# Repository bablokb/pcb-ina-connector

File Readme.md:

PCB INA-Connector
=================

This is a support PCB for Adafruit's INA219, INA260 and INA3221
breakouts. Connect the power-source to one of the connectors
on the V-IN side, the load to one of the connectors on the V-OUT
side and the INA-breakout to the screwterminal on the back.

V-IN supports

  - a JST-PH2 connector (typically for a LiPo) or
  - a two-pin DuPont 2.54mm pitch header or
  - a 5.5/2.1mm barrel jack

V-OUT suports

  - an AKL-182 socket or
  - a two-pin DuPont 2.54mm pitch header
    
The AKL-182 socket takes AKL-169 plugs. I use these with various
adapter wires, equiped e.g. with micro-USB, USB-C, JST-PH2 on the
other end.
As an alternative, you could use plain 3.5mm screw-terminals.

The footprint inbetween V-IN and V-OUT is for a mini toggle
switch, e.g.
<https://aliexpress.com/item/1005004692981776.html>.

You should also connect GND of this PCB to the INA-breakout if it
does not share GND somewhere else. Likewise for the INA3221
(which has three channels), use and connect three of these
PCBs:

Schematic
---------

Layout
------

3D-Views
--------

3D-Model
--------

In the directory `3D` there is an OpenSCAD-model for a
holder that takes an INA3221 and three off the PCBs.

License
-------

[![CC BY-SA 4.0][cc-by-sa-shield]][cc-by-sa]

This work is licensed under a
[Creative Commons Attribution-ShareAlike 4.0 International
License][cc-by-sa].

[![CC BY-SA 4.0][cc-by-sa-image]][cc-by-sa]

[cc-by-sa]: http://creativecommons.org/licenses/by-sa/4.0/
[cc-by-sa-image]: https://licensebuttons.net/l/by-sa/4.0/88x31.png
[cc-by-sa-shield]:
https://img.shields.io/badge/License-CC%20BY--SA%204.0-lightgrey.svg

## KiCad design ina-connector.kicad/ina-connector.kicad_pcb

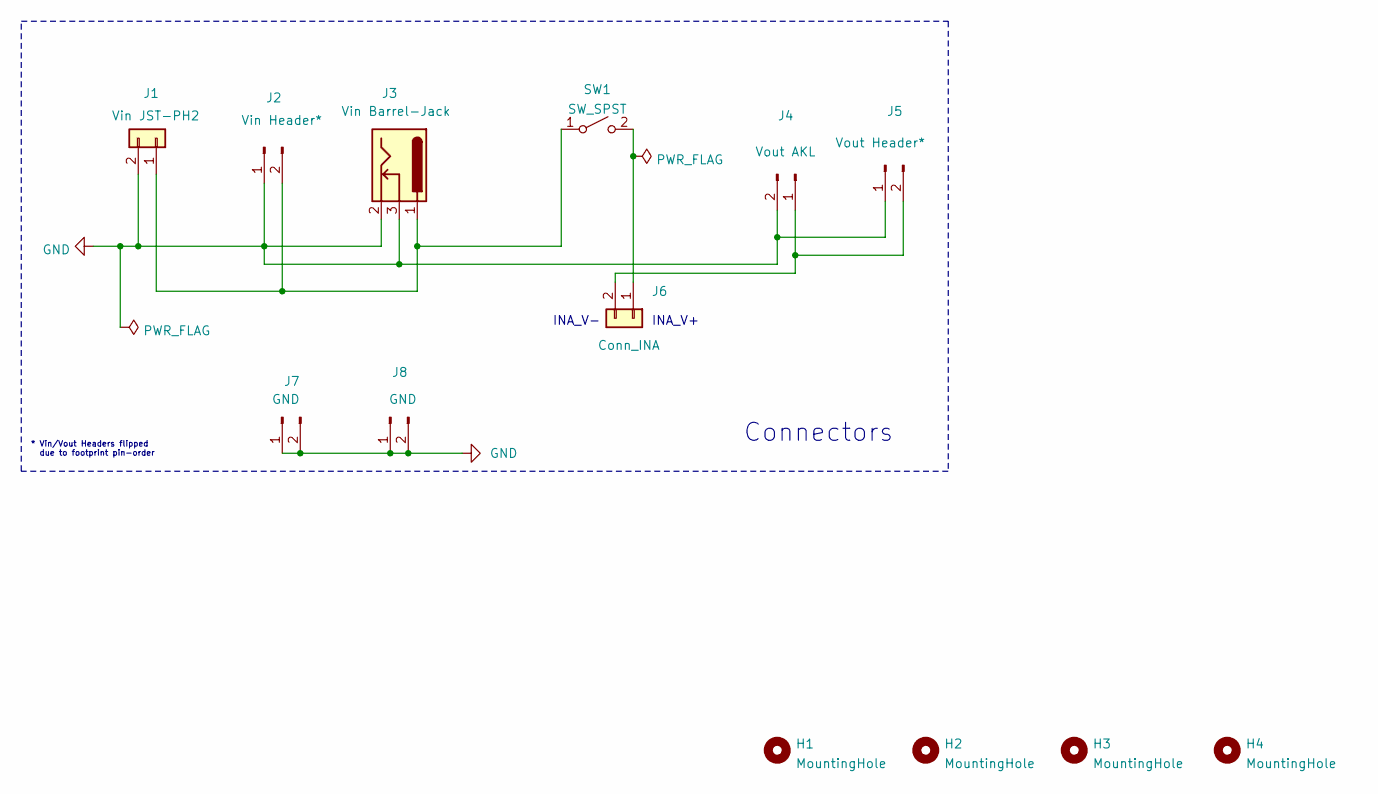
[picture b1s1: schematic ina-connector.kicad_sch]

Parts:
H1, H2, H3, H4: MountingHole; MountingHole_2.5mm
J1: Vin JST-PH2; JST_PH_S2B-PH-SM4-TB_1x02-1MP_P2.00mm_Horizontal
J2: Vin Header*; PinHeader_1x02_P2.54mm_Horizontal
J3: Vin Barrel-Jack; BarrelJack_CUI_PJ-102AH_Horizontal
J4: Vout AKL; TerminalBlock_MetzConnect_Type182_PT11302HBBN_1x02_P3.50mm_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
J5: Vout Header*; PinHeader_1x02_P2.54mm_Horizontal
J6: Conn_INA; TerminalBlock_MetzConnect_Type059_RT06302HBWC_1x02_P3.50mm_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
J7, J8: GND; PinHeader_1x02_P2.54mm_Horizontal
SW1: SW_SPST; Kippschalter_On-Off

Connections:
GND: J1.2, J2.1, J3.2, J3.3, J4.2, J5.1, J7.1, J7.2, J8.1, J8.2
unnamed: J1.1, J2.2, J3.1, SW1.1 (A)
unnamed: J4.1, J5.2, J6.2
unnamed: J6.1, SW1.2 (B)

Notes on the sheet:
* Vin/Vout Headers flipped due to footprint pin-order
INA_V-
INA_V+
Connectors

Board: 2 copper layers, 13 parts (0 on the bottom side), 4 nets, no tracks yet.

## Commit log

2025-02-08 added 3D model for INA3221 plus 3 connectors
2025-02-08 add image of 3D-holder
2025-02-10 Rev. 1.10: use thermal reliefs
2025-02-19 basic implementation of cover
2025-02-19 rotate INA3221-holder, i.e. move the Stemma/Qt connector on the front
2025-02-19 add support walls
2025-02-19 added cutouts for ina-connectors
2025-02-19 added cutouts for switches
2025-02-19 add cutout for Stemma/Qt
2025-02-20 moved holes for switches a bit
2025-02-20 enlarged cutout
2025-02-20 enlarge cutouts up to the top
2025-02-20 larger cutout for Stemma/Qt
2025-02-20 added support for INA3221 screw-terminals
2025-04-05 add image of INA3221 with connectors
